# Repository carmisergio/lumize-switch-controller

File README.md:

# Lumize Switch Controller

A rack-mountable device for receiving input from physical wall switches and using it in a home automation situation

## Goal

When designing the home automation system for a reasonably sized attic, I came to the conclusion
that there aren't any good commercial solutions for reliably reading button input from switches mounted
in regular wall boxes. So I decided to design my own.

To avoid the complication (and waste of space) of having a network connected microcontroller in
each wall box, I chose to implement a solution based on a central device, with cables running to each button.
This poses the challenge of bringing upwards of four signals all the way from each corner of the floor
to a central location. The only cheap and easy to come by cable that has enough conductors is UTP cable,
usually used for ethernet networks. The cable is terminated as RJ45 male inside the wall box, and into a
patch panel at the central location.

## Switches

For my system, I wanted to use regular italian style wall switches, so I needed a way of interfacing
the RJ45 to some bare wire to be plugged into the buttons. This is done with a simple PCB i call the
"Switch Terminator Board", which exposes the connections as screw terminals.

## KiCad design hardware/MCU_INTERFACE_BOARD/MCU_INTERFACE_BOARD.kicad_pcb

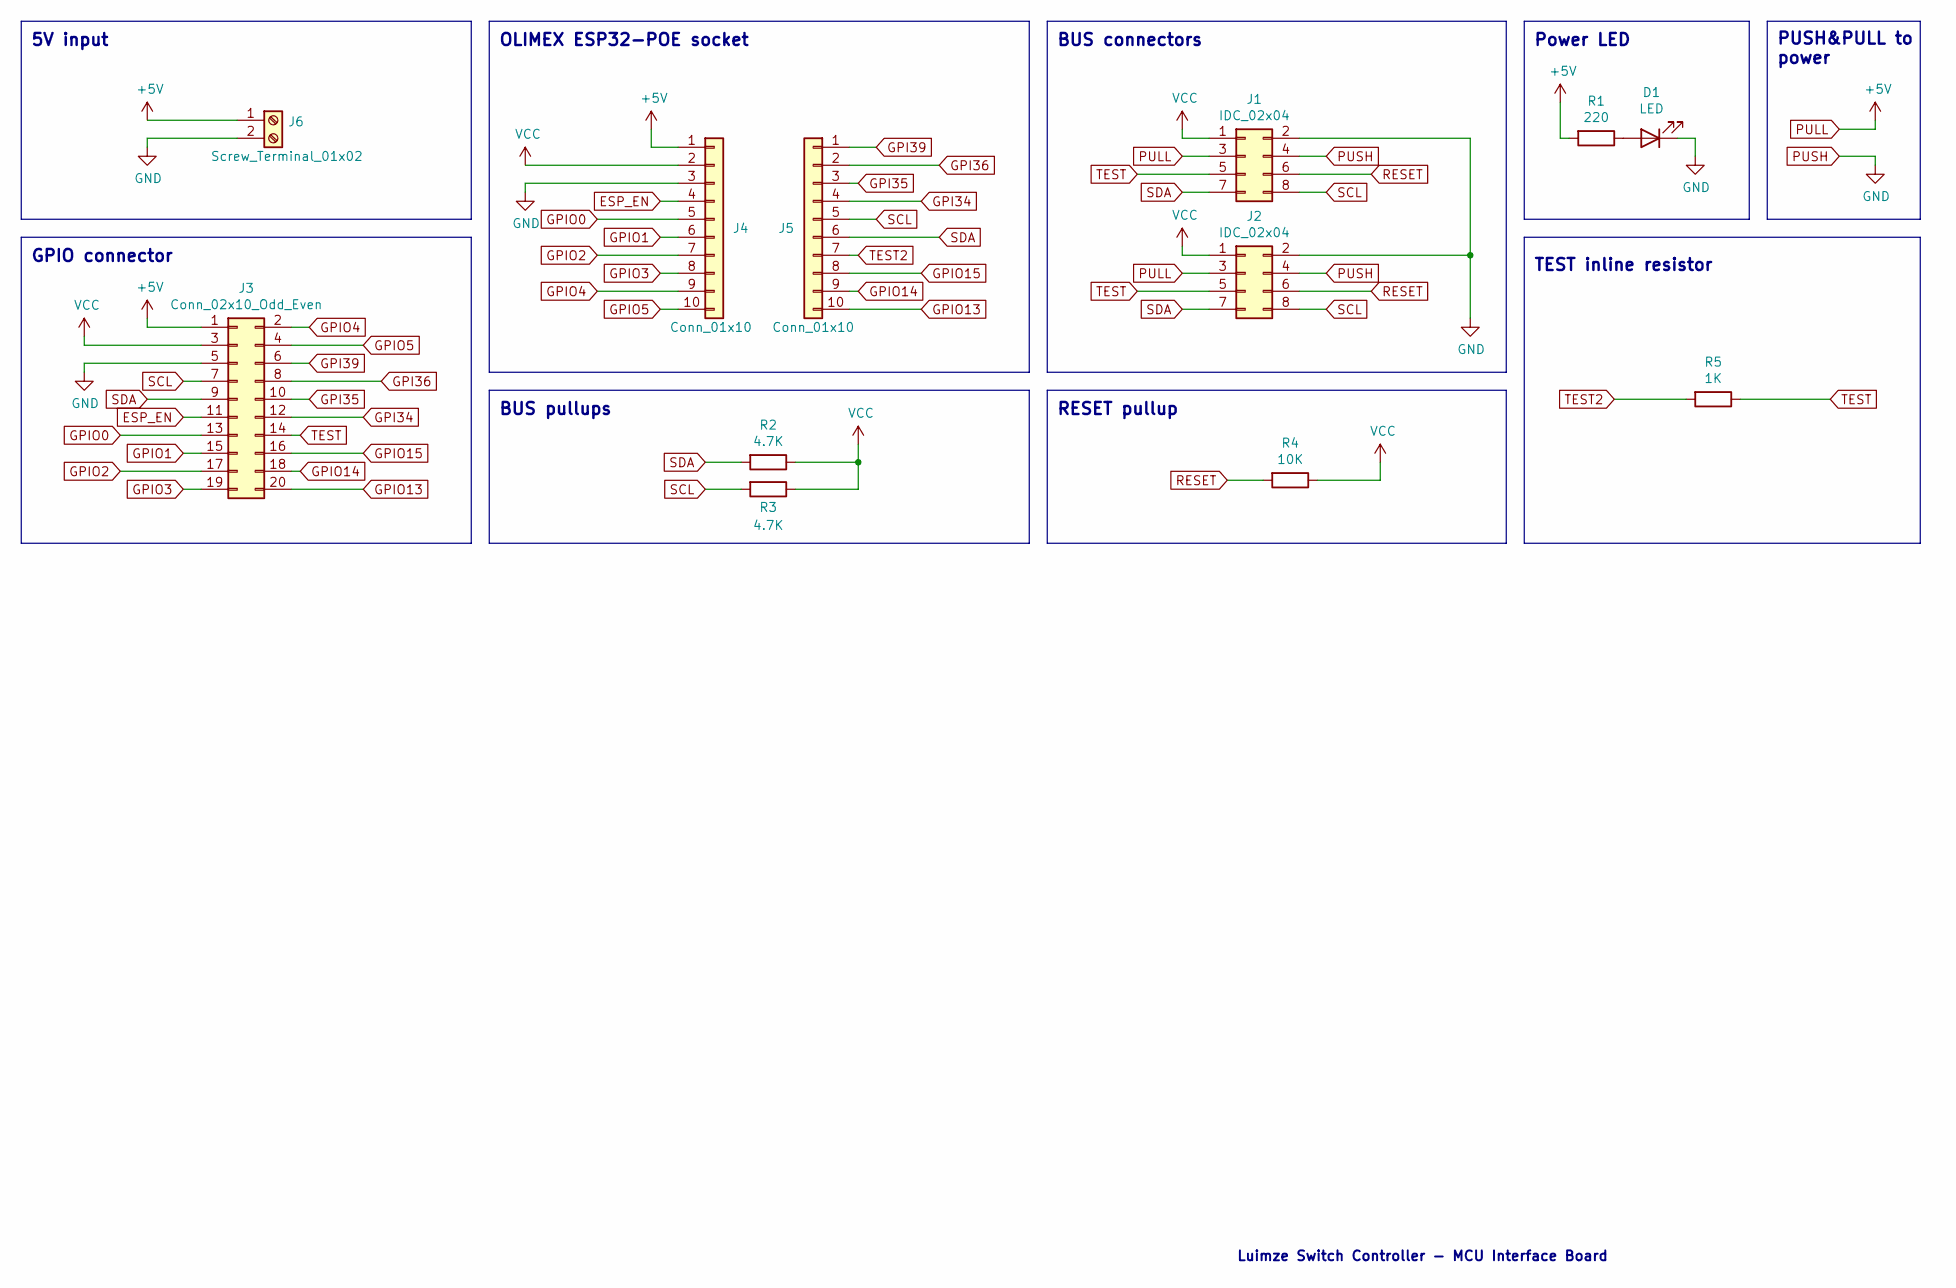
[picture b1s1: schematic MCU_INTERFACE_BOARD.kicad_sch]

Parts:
D1: LED; LED_0805_2012Metric
J1, J2: IDC_02x04; IDC-Header_2x04_P2.54mm_Vertical
J3: Conn_02x10_Odd_Even; IDC-Header_2x10_P2.54mm_Vertical
J4, J5: Conn_01x10; PinHeader_1x10_P2.54mm_Vertical
J6: Screw_Terminal_01x02; TerminalBlock_4Ucon_1x02_P3.50mm_Horizontal
R1: 220; R_Axial_DIN0207_L6.3mm_D2.5mm_P10.16mm_Horizontal
R2, R3: 4.7K; R_Axial_DIN0207_L6.3mm_D2.5mm_P10.16mm_Horizontal
R4: 10K; R_Axial_DIN0207_L6.3mm_D2.5mm_P10.16mm_Horizontal
R5: 1K; R_Axial_DIN0207_L6.3mm_D2.5mm_P10.16mm_Horizontal

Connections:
ESP_EN: J3.11, J4.4
GPI34: J3.12, J5.4
GPI35: J3.10, J5.3
GPI36: J3.8, J5.2
GPI39: J3.6, J5.1
GPIO0: J3.13, J4.5
GPIO1: J3.15, J4.6
GPIO2: J3.17, J4.7
GPIO3: J3.19, J4.8
GPIO4: J3.2, J4.9
GPIO5: J3.4, J4.10
GPIO13: J3.20, J5.10
GPIO14: J3.18, J5.9
GPIO15: J3.16, J5.8
unnamed: D1.2 (A), R1.1
PULL: J1.3, J2.3, J3.1, J4.1, J6.1, R1.2
PUSH: D1.1 (K), J1.2, J1.4, J2.2, J2.4, J3.5, J4.3, J6.2
RESET: J1.6, J2.6, R4.2
SCL: J1.8, J2.8, J3.7, J5.5, R3.2
SDA: J1.7, J2.7, J3.9, J5.6, R2.2
TEST: J1.5, J2.5, J3.14, R5.1
TEST2: J5.7, R5.2
VCC: J1.1, J2.1, J3.3, J4.2, R2.1, R3.1, R4.1

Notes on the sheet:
TEST inline resistor
BUS pullups
OLIMEX ESP32-POE socket
PUSH&PULL to power
GPIO connector
BUS connectors
Luimze Switch Controller - MCU Interface Board
5V input
Power LED
RESET pullup

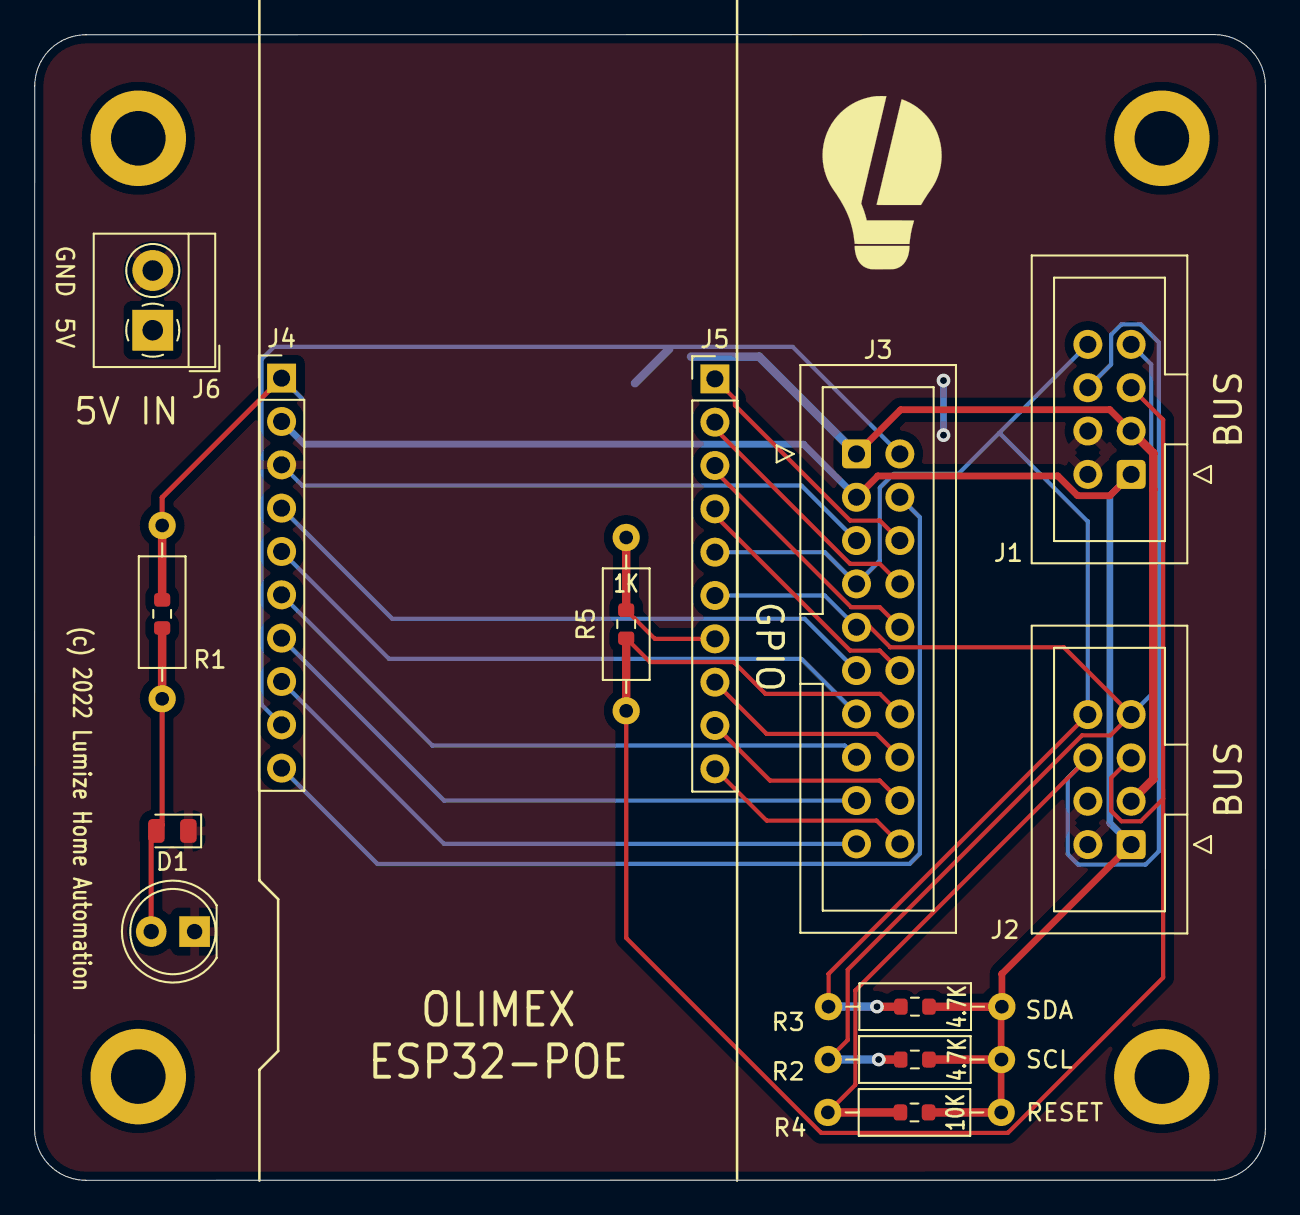
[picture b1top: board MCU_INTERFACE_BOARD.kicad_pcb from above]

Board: 2 copper layers, 72.2 x 67.2 mm, 12 parts (0 on the bottom side), 23 nets.

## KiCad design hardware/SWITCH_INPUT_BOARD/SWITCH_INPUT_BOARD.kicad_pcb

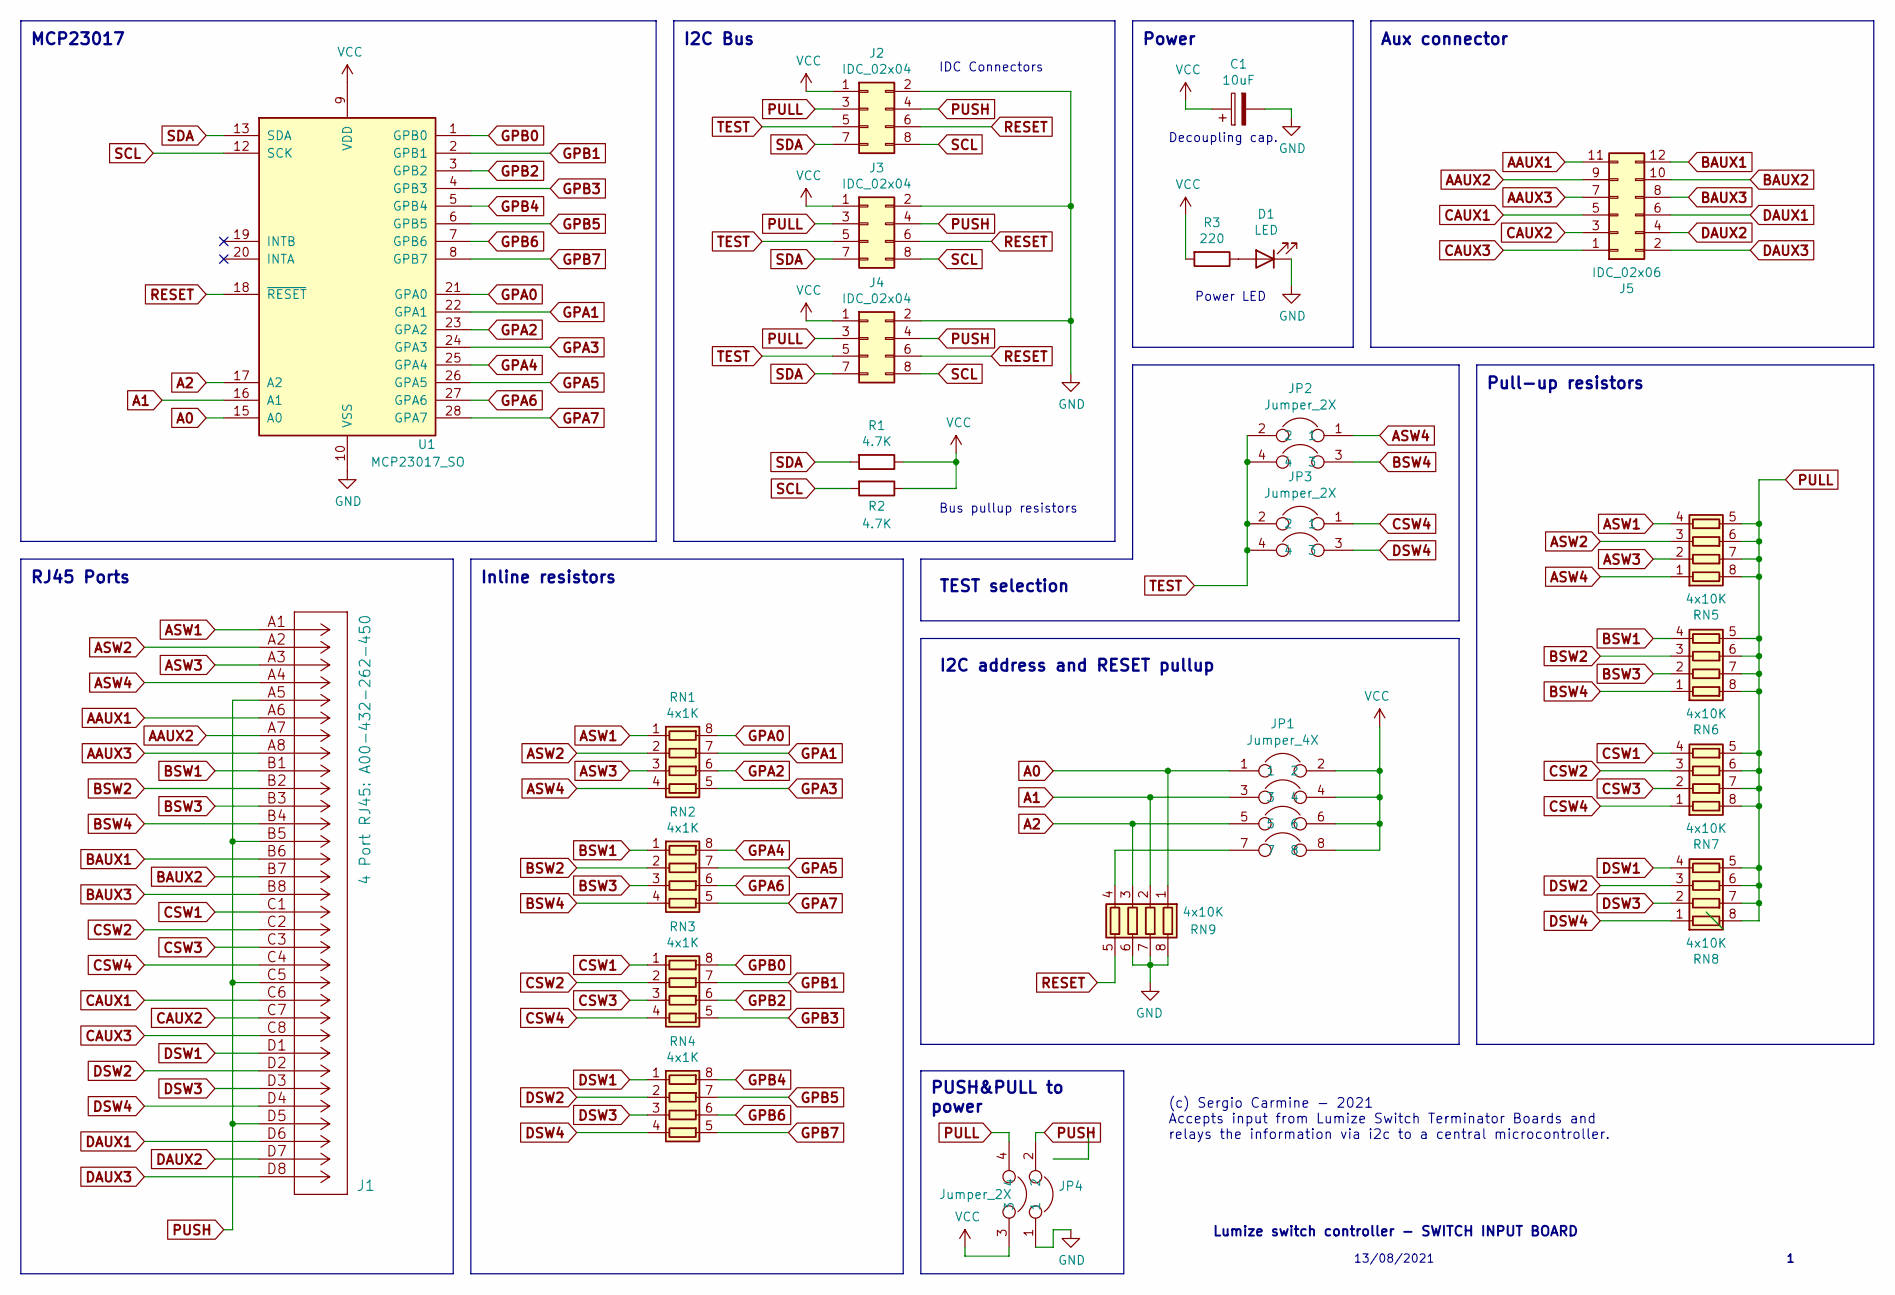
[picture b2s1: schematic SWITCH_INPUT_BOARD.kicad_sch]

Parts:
C1: 10uF; CP_Radial_D4.0mm_P1.50mm
D1: LED; LED_0805_2012Metric
J1: 4 Port RJ45: A00-432-262-450; A00-432-262-450
J2, J3, J4: IDC_02x04; IDC-Header_2x04_P2.54mm_Vertical
J5: IDC_02x06; IDC-Header_2x06_P2.54mm_Vertical
JP1: Jumper_4X; PinHeader_2x04_P2.54mm_Vertical
JP2, JP3, JP4: Jumper_2X; PinHeader_2x02_P2.54mm_Vertical
R1, R2: 4.7K; R_Axial_DIN0207_L6.3mm_D2.5mm_P10.16mm_Horizontal
R3: 220; R_Axial_DIN0207_L6.3mm_D2.5mm_P10.16mm_Horizontal
RN1, RN2, RN3, RN4: 4x1K; R_Array_Convex_4x1206
RN5, RN6, RN7, RN8, RN9: 4x10K; R_Array_Convex_4x1206
U1: MCP23017_SO; SOIC-28W_7.5x17.9mm_P1.27mm

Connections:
A0: JP1.1, RN9.1 (R1.1), U1.15 (A0)
A1: JP1.3, RN9.2 (R2.1), U1.16 (A1)
A2: JP1.5, RN9.3 (R3.1), U1.17 (A2)
AAUX1: J1.A6, J5.11
AAUX2: J1.A7, J5.9
AAUX3: J1.A8, J5.7
ASW1: J1.A1, RN1.1 (R1.1), RN5.4 (R4.1)
ASW2: J1.A2, RN1.2 (R2.1), RN5.3 (R3.1)
ASW3: J1.A3, RN1.3 (R3.1), RN5.2 (R2.1)
ASW4: J1.A4, JP2.1, RN1.4 (R4.1), RN5.1 (R1.1)
BAUX1: J1.B6, J5.12
BAUX2: J1.B7, J5.10
BAUX3: J1.B8, J5.8
BSW1: J1.B1, RN2.1 (R1.1), RN6.4 (R4.1)
BSW2: J1.B2, RN2.2 (R2.1), RN6.3 (R3.1)
BSW3: J1.B3, RN2.3 (R3.1), RN6.2 (R2.1)
BSW4: J1.B4, JP2.3, RN2.4 (R4.1), RN6.1 (R1.1)
CAUX1: J1.C6, J5.5
CAUX2: J1.C7, J5.3
CAUX3: J1.C8, J5.1
CSW1: J1.C1, RN3.1 (R1.1), RN7.4 (R4.1)
CSW2: J1.C2, RN3.2 (R2.1), RN7.3 (R3.1)
CSW3: J1.C3, RN3.3 (R3.1), RN7.2 (R2.1)
CSW4: J1.C4, JP3.1, RN3.4 (R4.1), RN7.1 (R1.1)
DAUX1: J1.D6, J5.6
DAUX2: J1.D7, J5.4
DAUX3: J1.D8, J5.2
DSW1: J1.D1, RN4.1 (R1.1), RN8.4 (R4.1)
DSW2: J1.D2, RN4.2 (R2.1), RN8.3 (R3.1)
DSW3: J1.D3, RN4.3 (R3.1), RN8.2 (R2.1)
DSW4: J1.D4, JP3.3, RN4.4 (R4.1), RN8.1 (R1.1)
GND: C1.2, D1.1 (K), J2.2, J3.2, J4.2, JP4.1, RN9.6 (R3.2), RN9.7 (R2.2), RN9.8 (R1.2), U1.10 (VSS); also elsewhere on the board
GPA0: RN1.8 (R1.2), U1.21 (GPA0)
GPA1: RN1.7 (R2.2), U1.22 (GPA1)
GPA2: RN1.6 (R3.2), U1.23 (GPA2)
GPA3: RN1.5 (R4.2), U1.24 (GPA3)
GPA4: RN2.8 (R1.2), U1.25 (GPA4)
GPA5: RN2.7 (R2.2), U1.26 (GPA5)
GPA6: RN2.6 (R3.2), U1.27 (GPA6)
GPA7: RN2.5 (R4.2), U1.28 (GPA7)
GPB0: RN3.8 (R1.2), U1.1 (GPB0)
GPB1: RN3.7 (R2.2), U1.2 (GPB1)
GPB2: RN3.6 (R3.2), U1.3 (GPB2)
GPB3: RN3.5 (R4.2), U1.4 (GPB3)
GPB4: RN4.8 (R1.2), U1.5 (GPB4)
GPB5: RN4.7 (R2.2), U1.6 (GPB5)
GPB6: RN4.6 (R3.2), U1.7 (GPB6)
GPB7: RN4.5 (R4.2), U1.8 (GPB7)
unnamed 48: D1.2 (A), R3.1; also elsewhere on the board
unnamed: JP1.7, RN9.4 (R4.1)
PULL: J2.3, J3.3, J4.3, JP4.4, RN5.5 (R4.2), RN5.6 (R3.2), RN5.7 (R2.2), RN5.8 (R1.2), RN6.5 (R4.2), RN6.6 (R3.2), RN6.7 (R2.2), RN6.8 (R1.2), RN7.5 (R4.2), RN7.6 (R3.2), RN7.7 (R2.2), RN7.8 (R1.2), RN8.5 (R4.2), RN8.6 (R3.2), RN8.7 (R2.2), RN8.8 (R1.2)
PUSH: J1.A5, J1.B5, J1.C5, J1.D5, J2.4, J3.4, J4.4, JP4.2
RESET: J2.6, J3.6, J4.6, RN9.5 (R4.2), U1.18 (~RESET)
SCL: J2.8, J3.8, J4.8, R2.2, U1.12 (SCK)
SDA: J2.7, J3.7, J4.7, R1.2, U1.13 (SDA)
TEST: J2.5, J3.5, J4.5, JP2.2, JP2.4, JP3.2, JP3.4
VCC: C1.1, J2.1, J3.1, J4.1, JP1.2, JP1.4, JP1.6, JP1.8, JP4.3, R1.1, R2.1, R3.2, U1.9 (VDD); also elsewhere on the board

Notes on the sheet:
Bus pullup resistors
Power LED
TEST selection
Pull-up resistors
I2C address and RESET pullup
Lumize switch controller - SWITCH INPUT BOARD
Power
MCP23017
Aux connector
IDC Connectors
13/08/2021
(c) Sergio Carmine - 2021 Accepts input from Lumize Switch Terminator Boards and relays the information via i2c to a central microcontroller.
Inline resistors
I2C Bus
RJ45 Ports
PUSH&PULL to power
Decoupling cap.

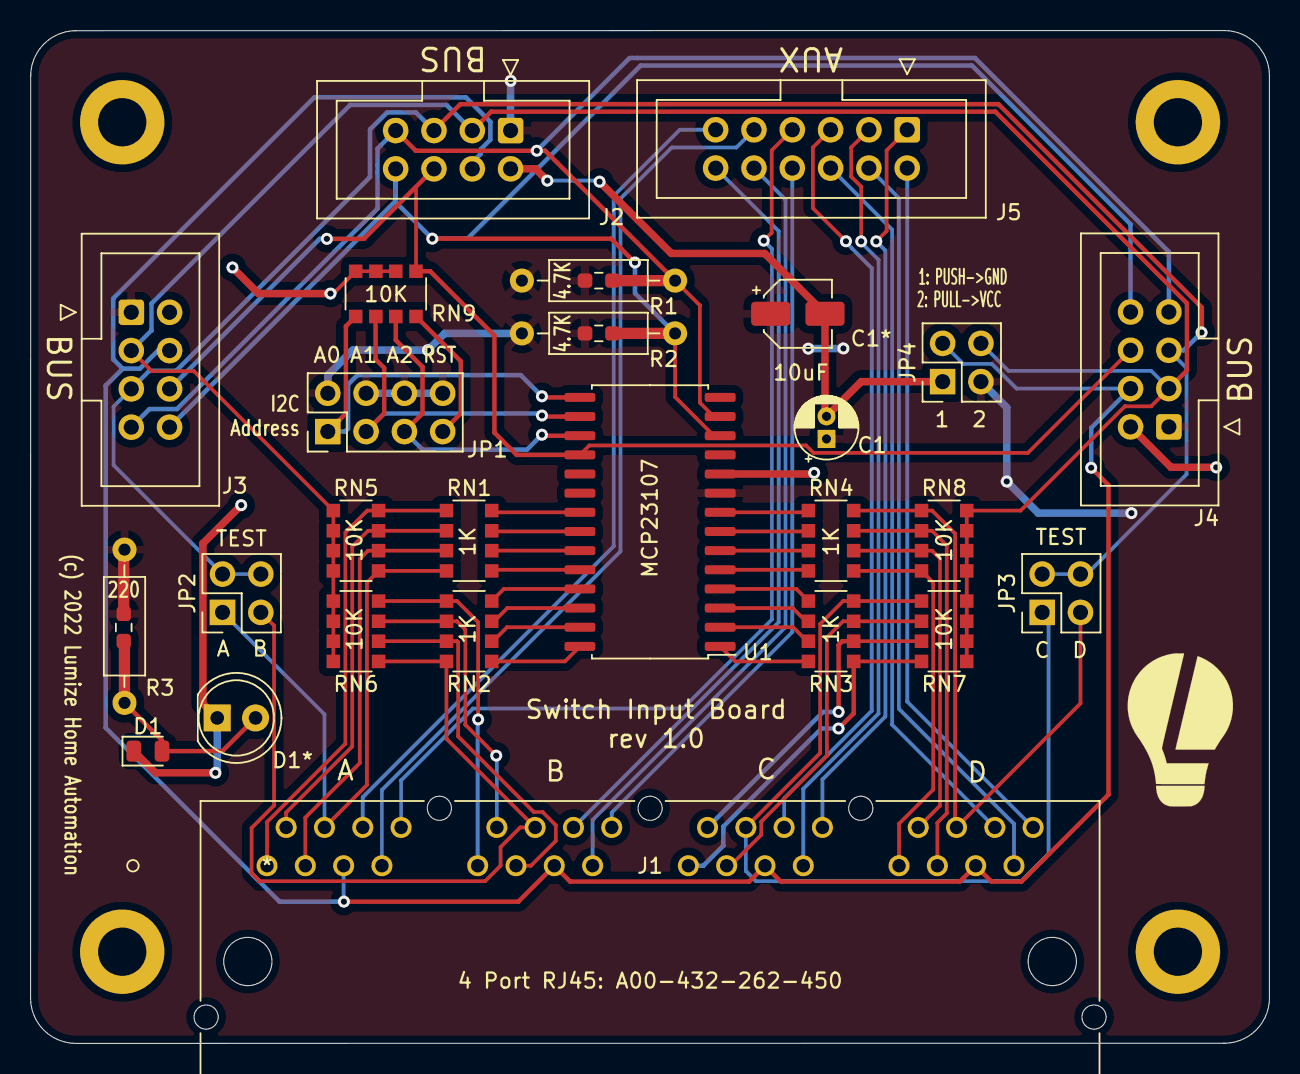
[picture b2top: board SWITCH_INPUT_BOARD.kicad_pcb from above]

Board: 2 copper layers, 82.2 x 67.2 mm, 26 parts (0 on the bottom side), 57 nets.

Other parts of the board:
C1*: CP_Elec_4x5.8
D1*: LED_D5.0mm

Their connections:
GND: C1*.2, D1*.1; also elsewhere on the board
unnamed 48: D1*.2; also elsewhere on the board
VCC: C1*.1; also elsewhere on the board

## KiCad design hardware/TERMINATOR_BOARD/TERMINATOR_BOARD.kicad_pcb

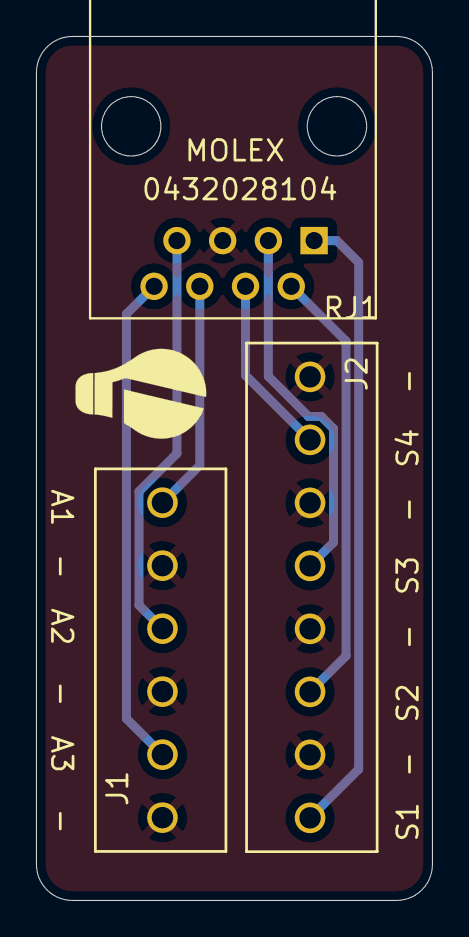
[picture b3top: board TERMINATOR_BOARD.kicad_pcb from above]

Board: 2 copper layers, 22.0 x 48.0 mm, 3 parts (0 on the bottom side), 8 nets.

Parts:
J1: *; CONN8_1776275-8
J2: *; CONN6_1776275-6
RJ1: 0432028104; RJ45-TH_0432028104

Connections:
AUX1: J2.1, RJ1.6
AUX2: J2.3, RJ1.7
AUX3: J2.5, RJ1.8
GND: J1.2, J1.4, J1.6, J1.8, J2.2, J2.4, J2.6, RJ1.5
SW1: J1.1, RJ1.1
SW2: J1.3, RJ1.2
SW3: J1.5, RJ1.3
SW4: J1.7, RJ1.4

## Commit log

2021-11-19 Switch input board rev 1.0
2021-11-19 Organize folder structure
2021-11-19 Do git stuff
2021-11-19 Write some readme:w
2021-11-20 Add Terminator board
2023-03-31 Finish development

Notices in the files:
hardware/MCU_INTERFACE_BOARD/MCU_INTERFACE_BOARD.kicad_pcb:
(c) 2022 Lumize Home Automation
parts and their libraries:
Copyright 2021 Accelerated Designs. All rights reserved.
